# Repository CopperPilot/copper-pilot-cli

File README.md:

<div align="center">
  <a href="https://copperpilot.ai">
    <picture>
      <source media="(prefers-color-scheme: dark)" srcset="https://github.com/CopperPilot/copper-pilot-cli/blob/main/docs/assets/logo-dark.png?raw=true">
      <source media="(prefers-color-scheme: light)" srcset="https://github.com/CopperPilot/copper-pilot-cli/blob/main/docs/assets/logo-light.png?raw=true">
      
    </picture>
  </a>
</div>

<div align="center">
  <h3>The AI for PCB design, in your terminal.</h3>
</div>

<div align="center">

</div>

<div align="center">

</div>

<br>

CopperPilot in your terminal: a thin, open-source client for CopperPilot electronics design agent, the best AI for PCB Design.

## Prerequisites

- Python 3.11 or newer
- A [CopperPilot](https://copperpilot.ai) account for login
- KiCad 10 on `PATH` only if you run [`examples/001_esp32`](examples/001_esp32) or [`examples/002_cm5_camera`](examples/002_cm5_camera)

## Install and run

```console
pip install copper-pilot-cli
copper-pilot
```

To let the agent import LCSC/EasyEDA parts (symbol, footprint and 3D model) with
`easyeda2kicad`, install the optional extra, which is AGPL-3.0 licensed:
`pip install "copper-pilot-cli[easyeda]"` (or
`uv tool install "copper-pilot-cli[easyeda]"`). Agent shell commands can run
command-line tools installed alongside the CLI even when pipx or `uv tool` keeps
them off your `PATH`.

The first interactive launch opens a browser for CopperPilot device login.
With no path argument, the current directory is the workspace and a new chat
starts immediately. Any existing directory is valid.

CopperPilot checks for feature updates once per day without delaying your work.
When a release adds a feature, it prints one line with the feature and
`copper-pilot update`. Use `copper-pilot update --check` to inspect the latest
release, or `copper-pilot update` to run the owning package manager's update.

```console
copper-pilot ./my-board
copper-pilot --resume
copper-pilot threads list
copper-pilot -n -m "Review this board" --json
copper-pilot -n -r          # resume the most recent thread's unfinished turn
copper-pilot --mode plan --effort intelligence -m "Survey and plan this board"
```

Long turns survive dropped connections, server restarts and LLM provider rate
limits (the CLI shows "High demand — waiting to continue" and resumes on its
own): the CLI keeps a
journal of the turn on your machine and resumes it automatically. If a turn
still does not finish (or the CLI was closed mid-turn), type `/resume` in the
TUI, run `copper-pilot -n -r`, or send "continue"; the turn picks up where it
left off without re-running finished tools. See
[Turn durability](docs/cli.md#turn-durability).

Both `copper-pilot` and `copper-pilot-cli` run the same program.
`copper-pilot --help` lists flags; [docs/cli.md](docs/cli.md) is the full
command reference.

Balanced effort is the default. Paid-plan users can select Intelligence with
`--effort intelligence` or interactive `/effort`; Intelligence runs on Gemini 4
Argon. Picking another model (`--model <id>`, `/model`) is turned off for now
(`ENABLE_MODEL_SELECTOR` in `copper_models.py`). Intelligence uses
server-owned survey subagents and shows their lifecycle through the existing
Deep Agents task rows; Intelligence Plan turns survey before writing a plan.

## Validate

```console
copper-pilot validate ./my-board
```

Runs a stage-gated graph of read-only reviewers over the KiCad workspace:
`kicad-cli` checks (ERC, DRC, schematic parity, board rules, Gerbers) plus
hosted Agent-mode reviewers, each scoped to one concern, in the order a hardware
engineer reviews a board. It never edits design files. The verdict, a
`REPORT.md`, and `next_actions.json` (only the earliest failing stage, worst
first) land in `.copperpilot/validate/latest/`; `--emit-fix-prompt` prints a
ready message for `copper-pilot --mode agent`. Exit codes: 0 pass, 1 fail,
2 config error, 3 incomplete, 4 not logged in or usage limit. See
[docs/validate.md](docs/validate.md).

## Use from Claude Code, Cursor, or Codex

CopperPilot stays the electronics agent. Copy
[`skills/copper-pilot-review/SKILL.md`](skills/copper-pilot-review/SKILL.md) into
your harness, or expose the same agent over MCP:

```console
claude mcp add copper-pilot -- copper-pilot mcp
```

Claude Code can also install the in-repo plugin:

```text
/plugin marketplace add CopperPilot/copper-pilot-cli
/plugin install copper-pilot
```

That plugin starts `copper-pilot mcp` (tools `status`, `ask`, `plan`, `run`,
`resume`, `threads_list`, `validate`) and adds `@copper-pilot` plus
`/copper-pilot-review`. Editors that speak the Agent Client Protocol, such as
Zed, can run `copper-pilot acp` after `pip install "copper-pilot-cli[acp]"`.
Setup for Cursor, Codex, Zed, and approvals: [docs/harness.md](docs/harness.md).

## Configuration

- Production API: `https://copperpilot.ai`
- Development override: `COPPER_PILOT_API_URL`
- User state: `~/.copper-pilot/.state`
- Project artifacts: `.copperpilot/`

Credentials are stored in a private, atomically replaced `auth.json`; on POSIX
the parent directory is mode `0700` and the file is mode `0600`.

## LangChain

```python
from copper_pilot_cli.copper_protocol import CopperEffort, CopperMode
from copper_pilot_cli.langchain import CopperPilotAgent
from helper import drc_violations, erc_errors, render_pcb, run

PLAN = CopperMode.PLAN

copper_pilot = CopperPilotAgent(
    workspace="esp32",
    effort=CopperEffort.INTELLIGENCE,
    model="claude-opus-5-5",  # optional; Intelligence defaults to Gemini 4 Argon
)

run(copper_pilot, "Build me an ESP32 dev board.", PLAN)
run(copper_pilot, "Let us build this plan.")
run(copper_pilot, "Inspect the PCB, check for any missing 3D models, and apply them accordingly.")

assert erc_errors() == 0
assert drc_violations() == 0
render_pcb("esp32.png")
```

`CopperPilotAgent` is a `Runnable`, not a chat model. It represents a complete
hosted agent run, including local tool requests. Use `as_langgraph()` for graph
composition or `as_compiled_subagent()` for explicit delegation from an outer
Deep Agent. The compatible `deepagents` runtime is installed and pinned by this
package.

That snippet is the runnable example in
[`examples/001_esp32`](examples/001_esp32). A phased CM5 camera carrier lives in
[`examples/002_cm5_camera`](examples/002_cm5_camera).

## Security boundary

The hosted agent may request local filesystem and shell tools. Reads and
searches run freely. Writes, edits, deletes, and shell commands are gated by
Manual approval by default. Auto permits only deterministic routine actions;
unknown actions still ask. YOLO must be selected explicitly. Shell commands
that reach outside the workspace (`find /`, `grep -r ~`, other projects under
the home directory, `docker`, `sudo`, `ssh`, `pkill`) count as dangerous: they
ask unless you run YOLO or Auto with dangerous shell commands auto-allowed, and
otherwise are refused when nobody can approve them (headless, MCP). See
[docs/cli.md](docs/cli.md#outside-the-workspace).

Filesystem, search, edit, and shell execution use Deep Agents' native
`FilesystemMiddleware` tools and `LocalShellBackend`; CopperPilot's adapter only
normalizes hosted tool names, approval decisions, and result envelopes.

Computer use, model/provider selection, local model execution, LangSmith
tracing, content telemetry, MCP **host**/plugin-runtime controls, and server
implementation code are not part of this package. A thin MCP **server**
(`copper-pilot mcp`) and an ACP **server** (`copper-pilot acp`) that delegate
to the hosted agent are.

See [UPSTREAM.md](UPSTREAM.md) and [NOTICE](NOTICE) for the retained Textual
client attribution.

To report a vulnerability, see [SECURITY.md](SECURITY.md).

## Development

```console
pip install -e ".[dev]"
make fmt
make lint
make test
```

`make test` runs `pytest -m "not live"`. Live tests skip unless a CopperPilot
credential is stored. Release tagging is `make release`. Details:
[docs/development.md](docs/development.md).

## Contributing

Bug reports, features, and pull requests are welcome. Please read
[CONTRIBUTING.md](CONTRIBUTING.md) and the
[Code of Conduct](CODE_OF_CONDUCT.md). Use the
[bug report form](https://github.com/CopperPilot/copper-pilot-cli/issues/new?template=bug_report.yml)
so we can reproduce the problem.

## License

[MIT](LICENSE).

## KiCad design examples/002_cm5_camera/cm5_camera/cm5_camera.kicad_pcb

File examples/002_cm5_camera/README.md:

# CM5 Camera Carrier

English in. KiCad out. CM5 camera carrier. Clean ERC, clean DRC, rendered PCB.

```python
from copper_pilot_cli.copper_protocol import CopperMode
from copper_pilot_cli.langchain import CopperPilotAgent
from helper import (
    already_done,
    discard_stale_plan,
    drc_violations,
    erc_errors,
    ensure_outer_gnd_zones,
    footprints_have_3d_models,
    format_netlist_contract,
    format_placement_spec,
    hosted_plan_prompt,
    inject_feedback,
    libraries_ready,
    lock_diff_tracks,
    lock_placement,
    netlist_matches,
    pcb_matches_schematic,
    pcb_segment_count,
    placement_feedback,
    placement_matches_spec,
    plan_has_spec,
    refill_zones,
    render_pcb,
    repair_drc,
    repair_erc,
    reset_pcb_copper,
    restore_pcb_if_wiped,
    route_headless,
    run,
    snapshot_pcb,
    solidify_plane_pad_connections,
    start,
    strip_high_speed_from_planes,
    telemetry_prompt,
    unconnected_count,
    zones_and_rules_ready,
)

PLAN = CopperMode.PLAN

PLAN_PROMPT = hosted_plan_prompt()
LIBS_PROMPT = (
    "Set up symbols and footprints for this CM5 camera project, reverse-engineered "
    "from Waveshare CM4-NANO-C (https://www.waveshare.com/wiki/CM4-NANO-C) and "
    "aligned with https://github.com/rapidanalysis/xerxes DF40 practice. "
    "Goal: project libraries must include every BOM row from the plan."
)
SCHEMATIC_PROMPT = (
    "Implement schematic capture in cm5_camera/cm5_camera.kicad_sch. "
    "Goal: kicad-cli `sch export netlist --format kicadxml` must contain these "
    "nets and connections:\\n"
    f"{format_netlist_contract()}\\n"
    "Use those net names. Populate Type_C1, U5, U1-U3, X1, Q1/Q2, L1-L3, J1 IMX219, "
    "U6, HDMI1, DSI1, TF1, PI1, Key1, and the CM5 DF40 module."
)
ERC_PROMPT = (
    "Run kicad-cli sch erc on cm5_camera/cm5_camera.kicad_sch and fix pin types, "
    "power flags, and floating inputs. Goal: zero ERC errors."
)
UPDATE_PCB_PROMPT = (
    "Update PCB footprints from the schematic. Goal: every schematic symbol with a "
    "footprint is on cm5_camera/cm5_camera.kicad_pcb, extra footprints are removed, "
    "and the netlist is imported."
)
LAYOUT_PROMPT = (
    "Lay out cm5_camera/cm5_camera.kicad_pcb from a wiped copper state. "
    "Goal: Edge.Cuts 55.0 x 40.0 mm with 3.0 mm corner radii and 4x M2.5 holes at "
    "board-local 3.5,3.5 / 3.5,36.5 / 51.5,3.5 / 51.5,36.5. Place and lock "
    "footprints to this board-local table (origin = SW of Edge.Cuts). J1 is east "
    "of center, not the board middle. HDMI1/DSI1 north, J2 east, TF1 west, "
    "Type_C1 south-west, PI1 west, Key1 south-east, DF40 on B.Cu. Silk: CM5 CAMERA.\\n"
    f"{format_placement_spec()}"
)
ZONES_PROMPT = (
    "Configure the 6-layer SIG-GND-SIG-PWR-GND-SIG stackup and pour planes. "
    "Goal: F.Cu, In1.Cu, In2.Cu, In3.Cu, In4.Cu, B.Cu present; solid GND zone on "
    "In1.Cu and In4.Cu; split CM5_5V and PWR_3V3 zones on In3.Cu; netclasses "
    "100Ohm_Diff (0.15 mm / 0.18 mm gap), 90Ohm_Diff (0.18 mm / 0.20 mm), "
    "Power_5V, Power_3V3 in cm5_camera.kicad_pro; refill zones. Do not autoroute."
)
ACK_PROMPT = (
    "Reply with the single word OK. Do not call tools. Do not edit files. "
    "Do not run kicad_autorouter or FreeRouting. Local headless routing already "
    "imported copper."
)
MODELS_3D_PROMPT = (
    "Inspect kicad-cli pcb render of cm5_camera/cm5_camera.kicad_pcb and assign "
    "3D models. Goal: the CM5 module, IMX219, Mini-HDMI, USB-C, USB-A, Micro SD, "
    "and GPIO header all have 3D models; re-render the top side."
)

copper_pilot = CopperPilotAgent(workspace="cm5_camera")
start(copper_pilot)
discard_stale_plan()
if not already_done(plan_has_spec):
    run(copper_pilot, PLAN_PROMPT, PLAN)
assert plan_has_spec()
if not already_done(libraries_ready):
    run(copper_pilot, LIBS_PROMPT)
assert libraries_ready()
if not already_done(netlist_matches):
    run(copper_pilot, SCHEMATIC_PROMPT)
assert netlist_matches()
if not already_done(lambda: erc_errors() == 0):
    run(copper_pilot, ERC_PROMPT)
    repair_erc()
assert erc_errors() == 0
if not already_done(pcb_matches_schematic):
    run(copper_pilot, UPDATE_PCB_PROMPT)
assert pcb_matches_schematic()

has_routes = pcb_segment_count() >= 50
keep_zones = already_done(placement_matches_spec) and already_done(zones_and_rules_ready)
if not has_routes:
    reset_pcb_copper(keep_zones=keep_zones)
    inject_feedback(
        "Tracks and vias were wiped"
        + ("." if keep_zones else ", along with zones.")
        + " Rebuild layout, stackup, and routing from the CM5 camera spec in this "
        "same conversation."
    )
if not already_done(placement_matches_spec):
    run(copper_pilot, LAYOUT_PROMPT)
    if not already_done(placement_matches_spec):
        run(copper_pilot, placement_feedback())
    if not already_done(placement_matches_spec):
        locked = lock_placement()
        inject_feedback(
            "Locked these footprints to the board-local assembly table: "
            + ", ".join(locked)
            + ". Continue from this placement; do not scatter parts."
        )
assert placement_matches_spec()

if not already_done(zones_and_rules_ready):
    run(copper_pilot, ZONES_PROMPT)
    if not already_done(zones_and_rules_ready):
        run(
            copper_pilot,
            "Finish the 6-layer stackup, 100Ohm_Diff / 90Ohm_Diff / Power_5V / "
            "Power_3V3 netclasses, GND pours on In1.Cu and In4.Cu, and CM5_5V plus "
            "PWR_3V3 pours on In3.Cu. Do not autoroute.",
        )
assert zones_and_rules_ready()

if not has_routes:
    diffs = route_headless(stage="diffs")
    if strip_high_speed_from_planes():
        diffs = route_headless(stage="diffs", passes=3)
        strip_high_speed_from_planes()
    lock_diff_tracks()
    leftover = unconnected_count()
    copper = snapshot_pcb()
    inject_feedback(telemetry_prompt(diffs, leftover=leftover))
    run(copper_pilot, ACK_PROMPT)
    restore_pcb_if_wiped(copper)
    assert high_speed_not_on_planes()

ensure_outer_gnd_zones()
solidify_plane_pad_connections()
if pcb_segment_count() < 700:
    gpio = route_headless(stage="gpio")
    if unconnected_count() > 0:
        gpio = route_headless(stage="gpio", passes=12)
    leftover = unconnected_count()
    copper = snapshot_pcb()
    inject_feedback(telemetry_prompt(gpio, leftover=leftover))
    run(copper_pilot, ACK_PROMPT)
    restore_pcb_if_wiped(copper)
refill_zones()
if drc_violations():
    repair_drc()
if not already_done(footprints_have_3d_models):
    run(copper_pilot, MODELS_3D_PROMPT)
assert footprints_have_3d_models()
render_pcb("cm5_camera.png")
assert high_speed_not_on_planes()
assert drc_violations() == 0
leftover = unconnected_count()
assert leftover == 0, f"{leftover} unconnected items remain"
```

```console
python examples/002_cm5_camera/main.py
```

Python 3.11+, `pip install -e .`, `copper-pilot auth login`, and KiCad 10 on `PATH`.

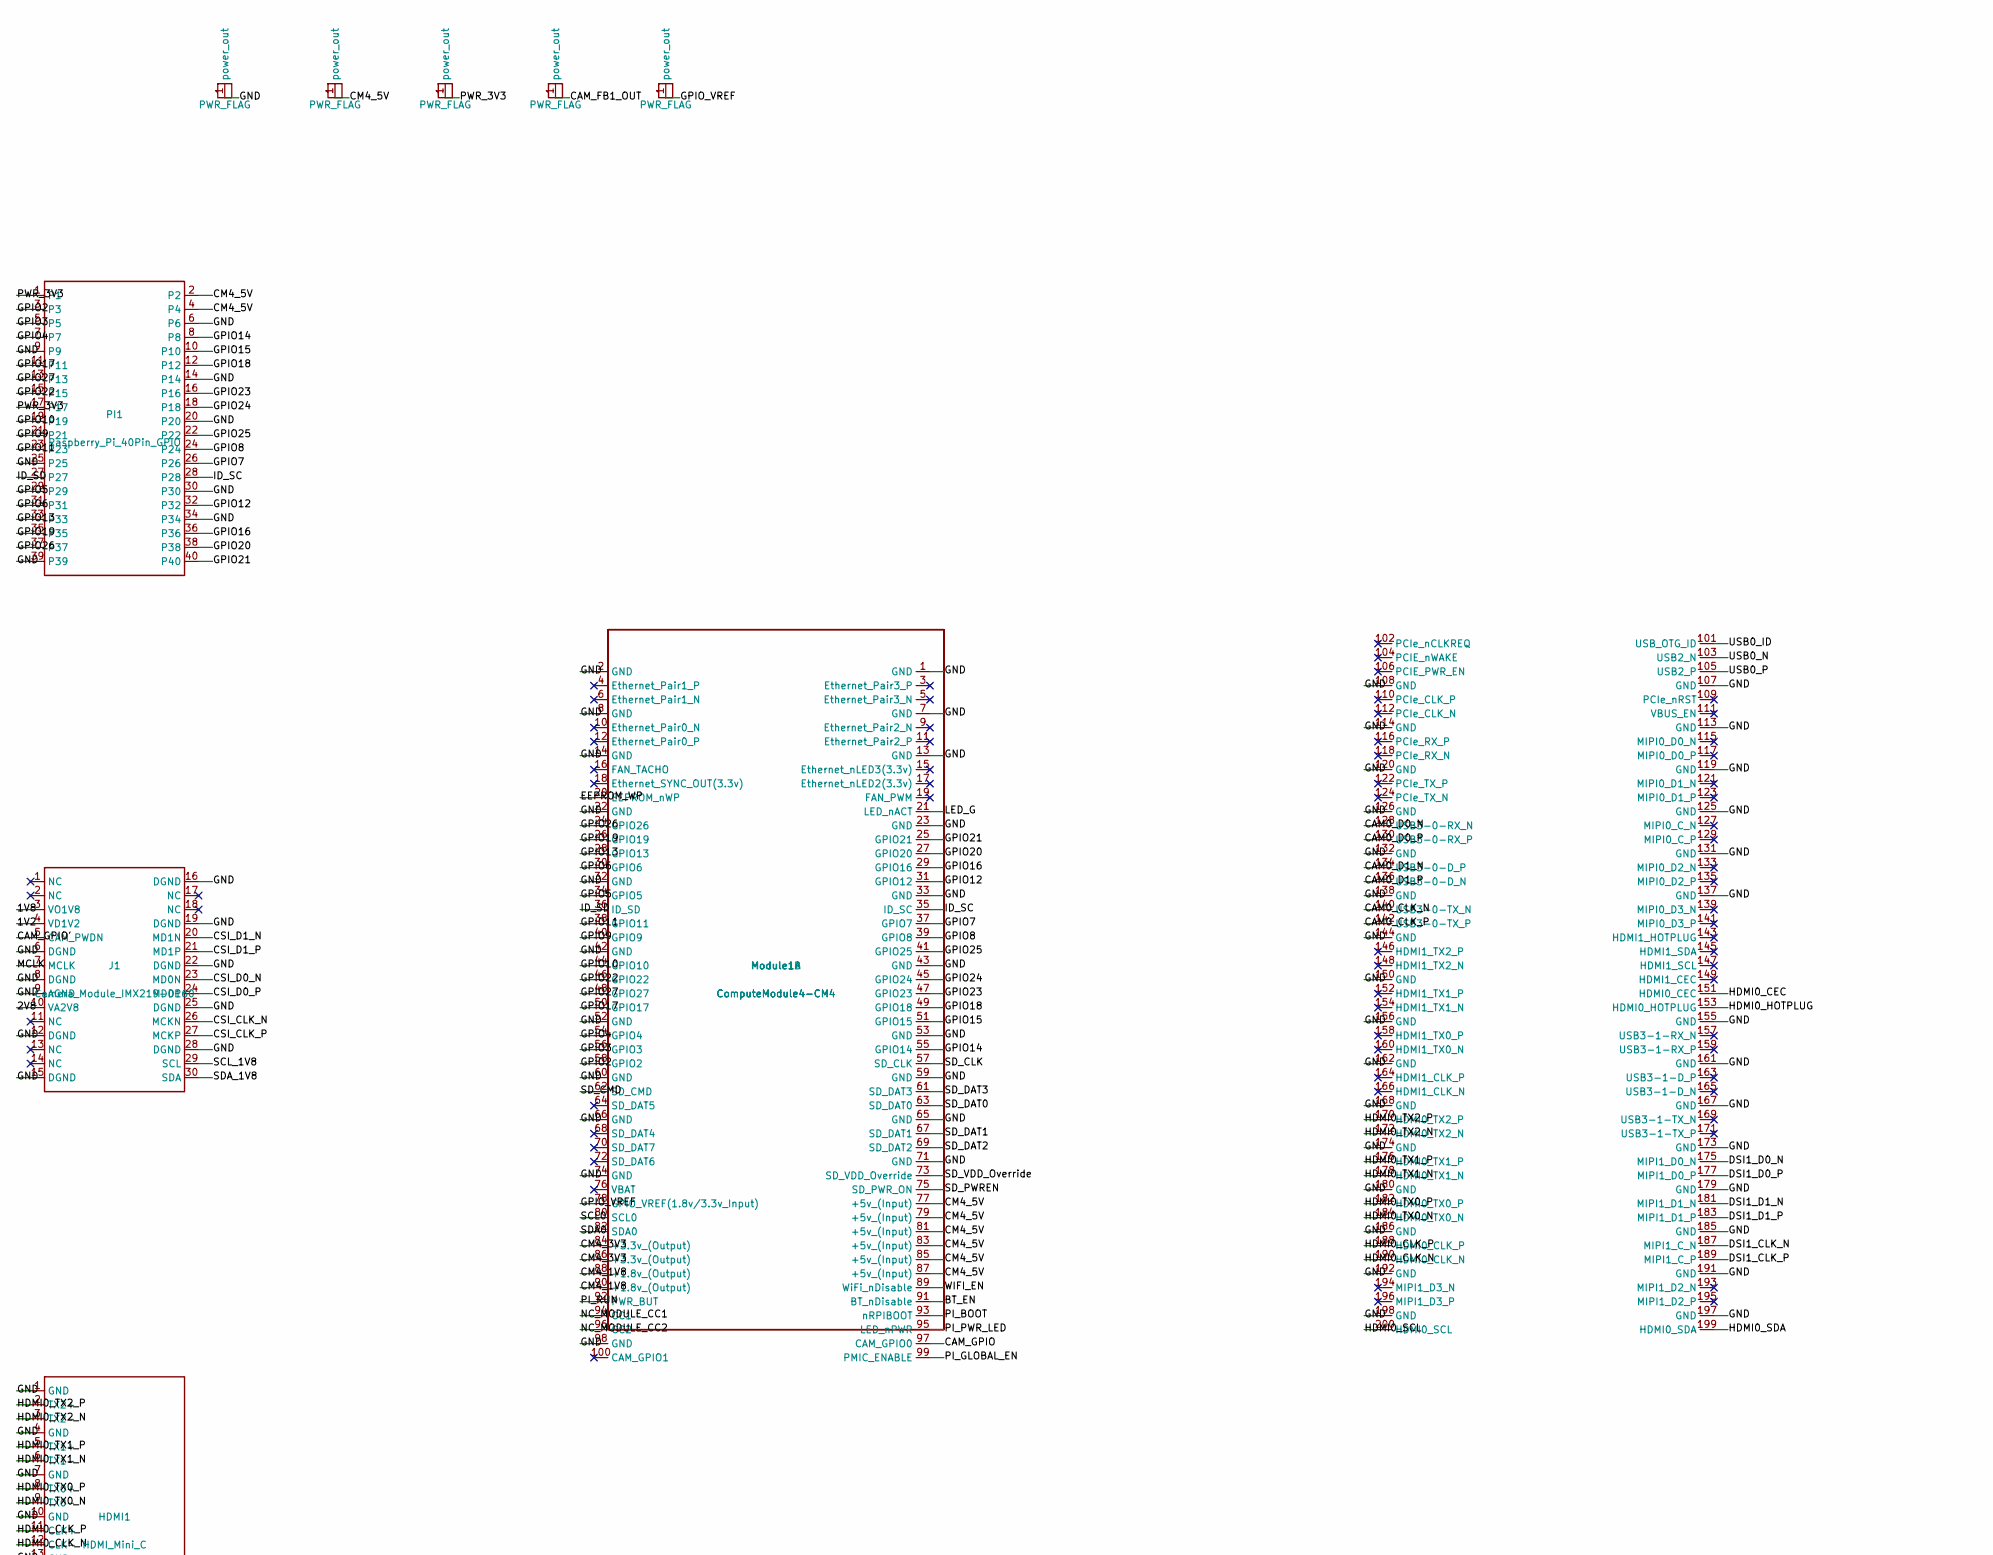
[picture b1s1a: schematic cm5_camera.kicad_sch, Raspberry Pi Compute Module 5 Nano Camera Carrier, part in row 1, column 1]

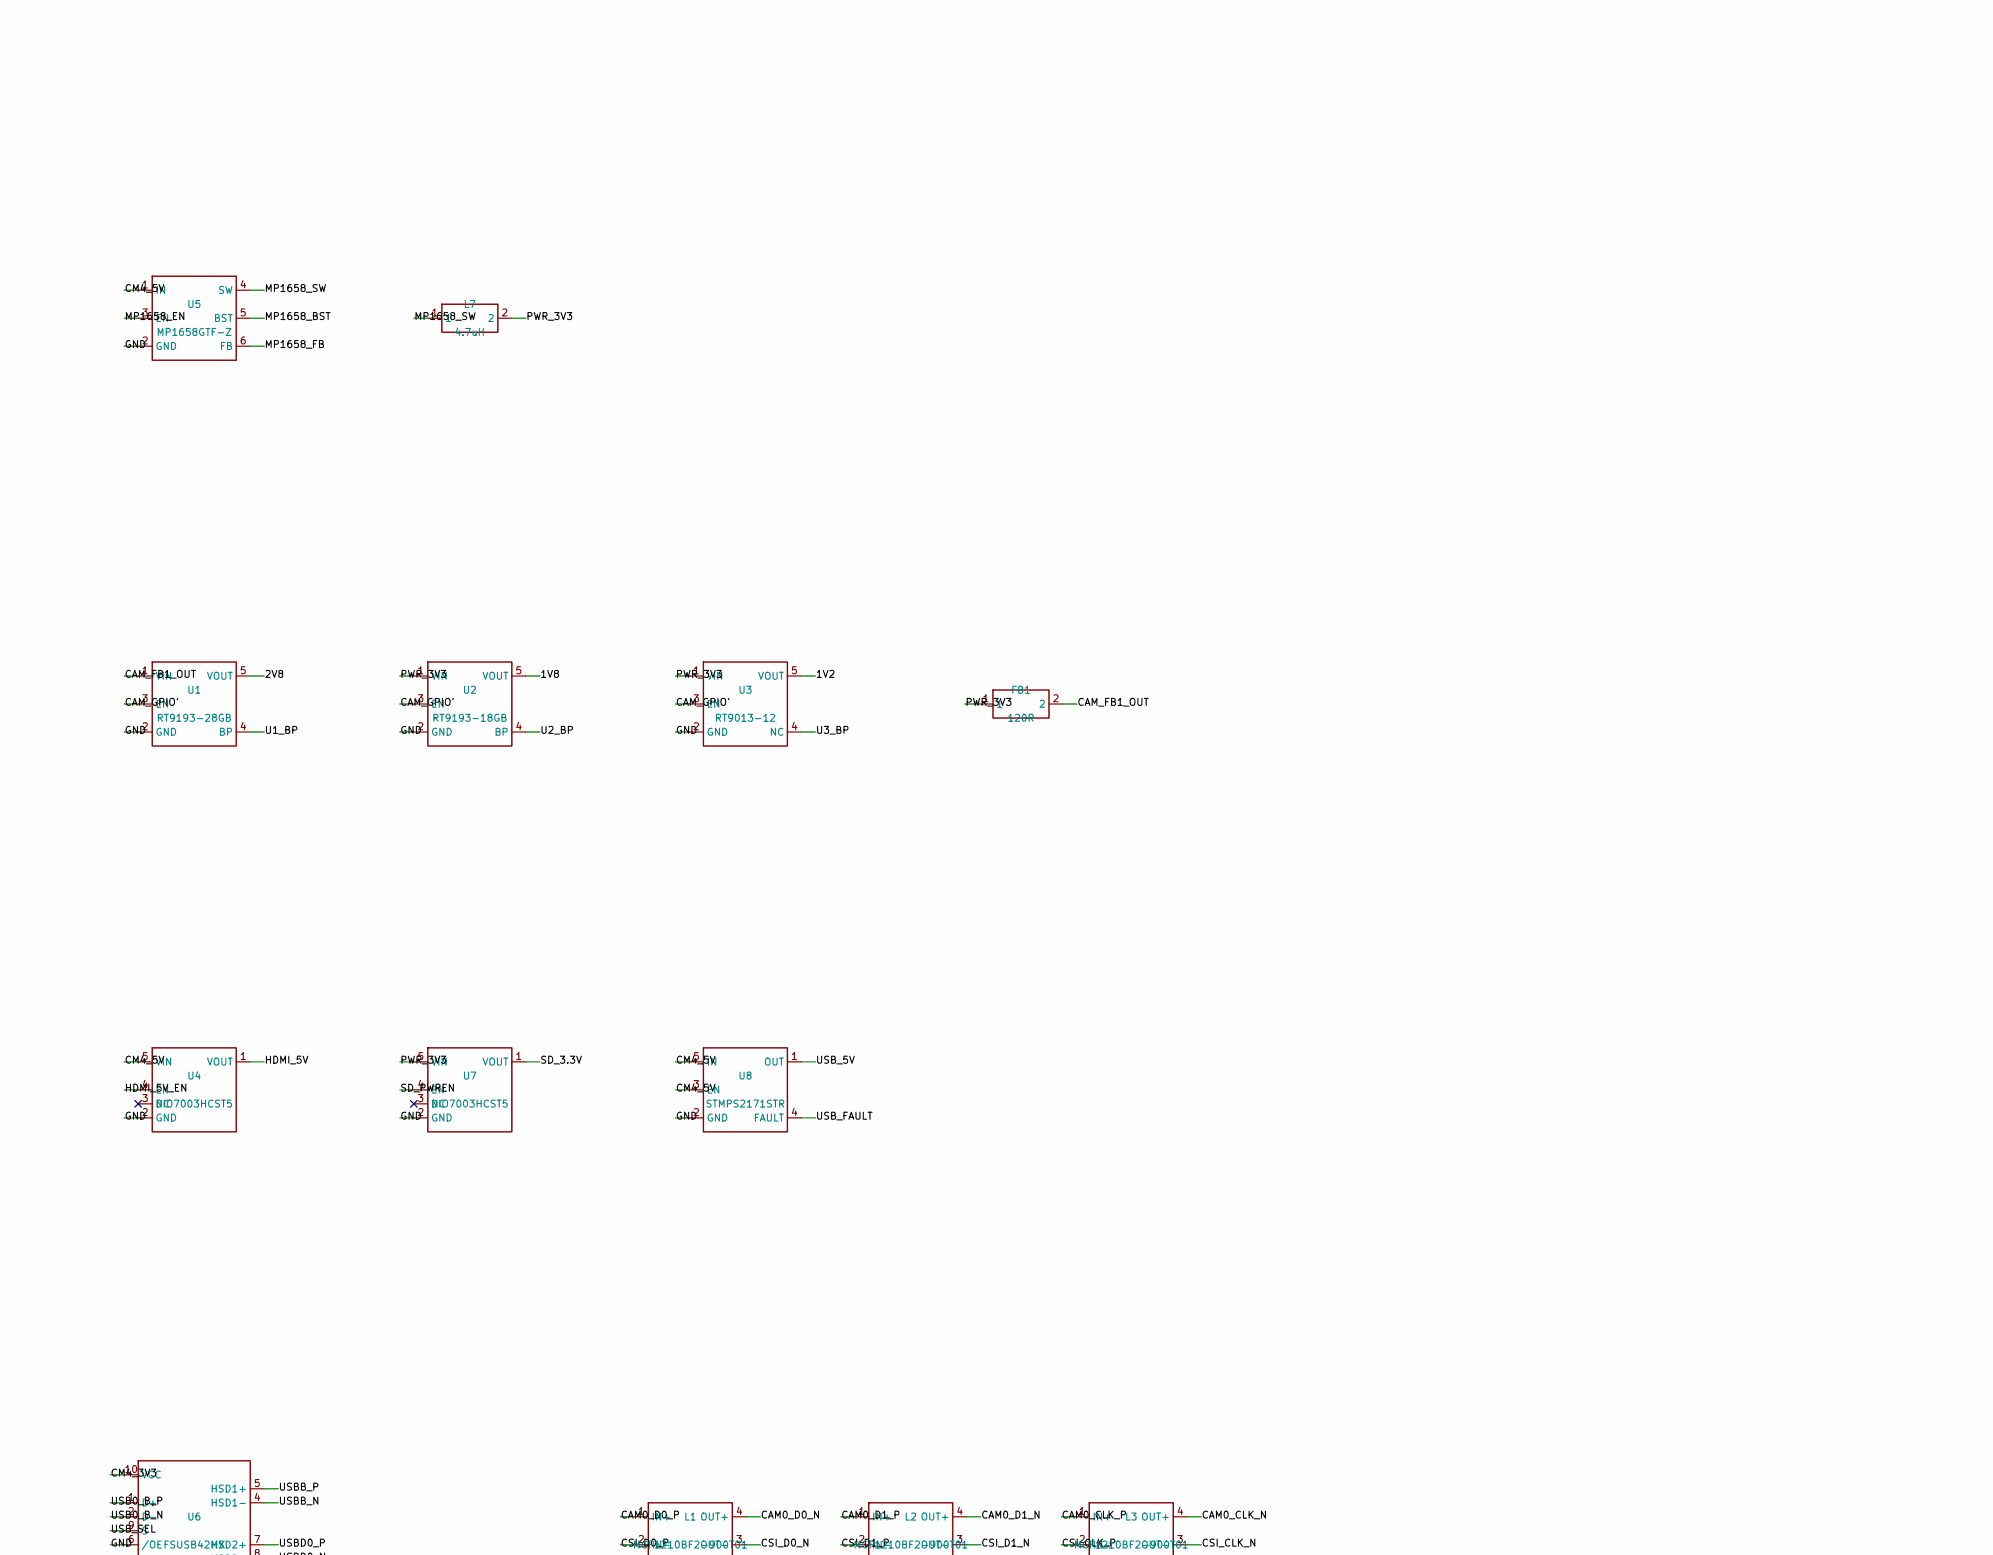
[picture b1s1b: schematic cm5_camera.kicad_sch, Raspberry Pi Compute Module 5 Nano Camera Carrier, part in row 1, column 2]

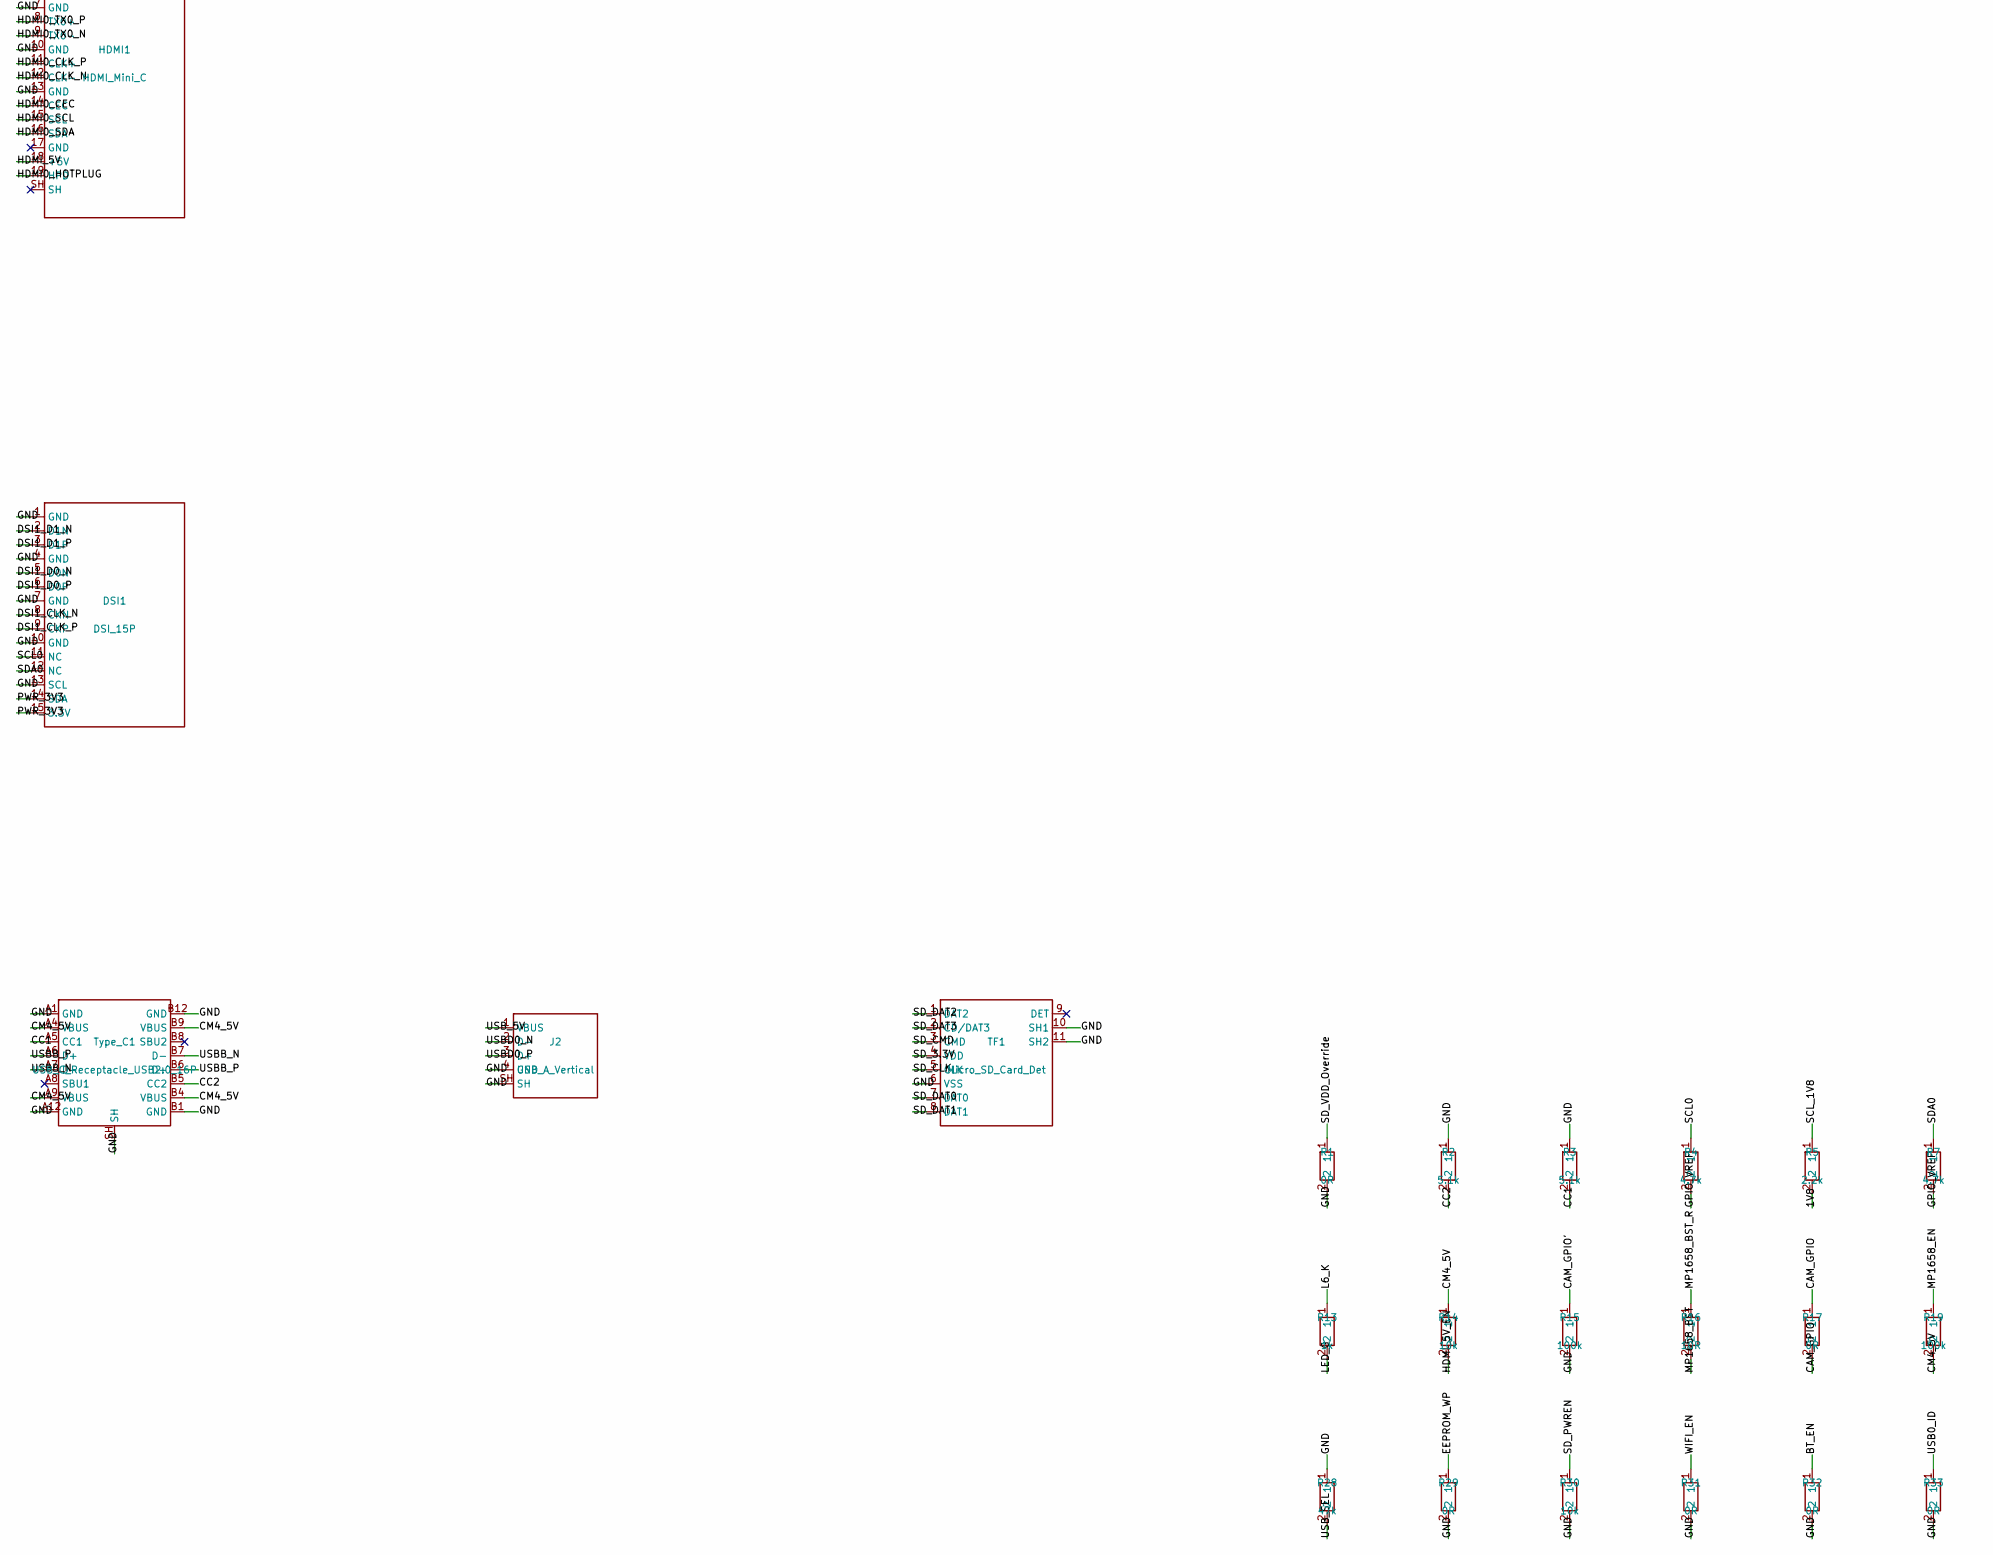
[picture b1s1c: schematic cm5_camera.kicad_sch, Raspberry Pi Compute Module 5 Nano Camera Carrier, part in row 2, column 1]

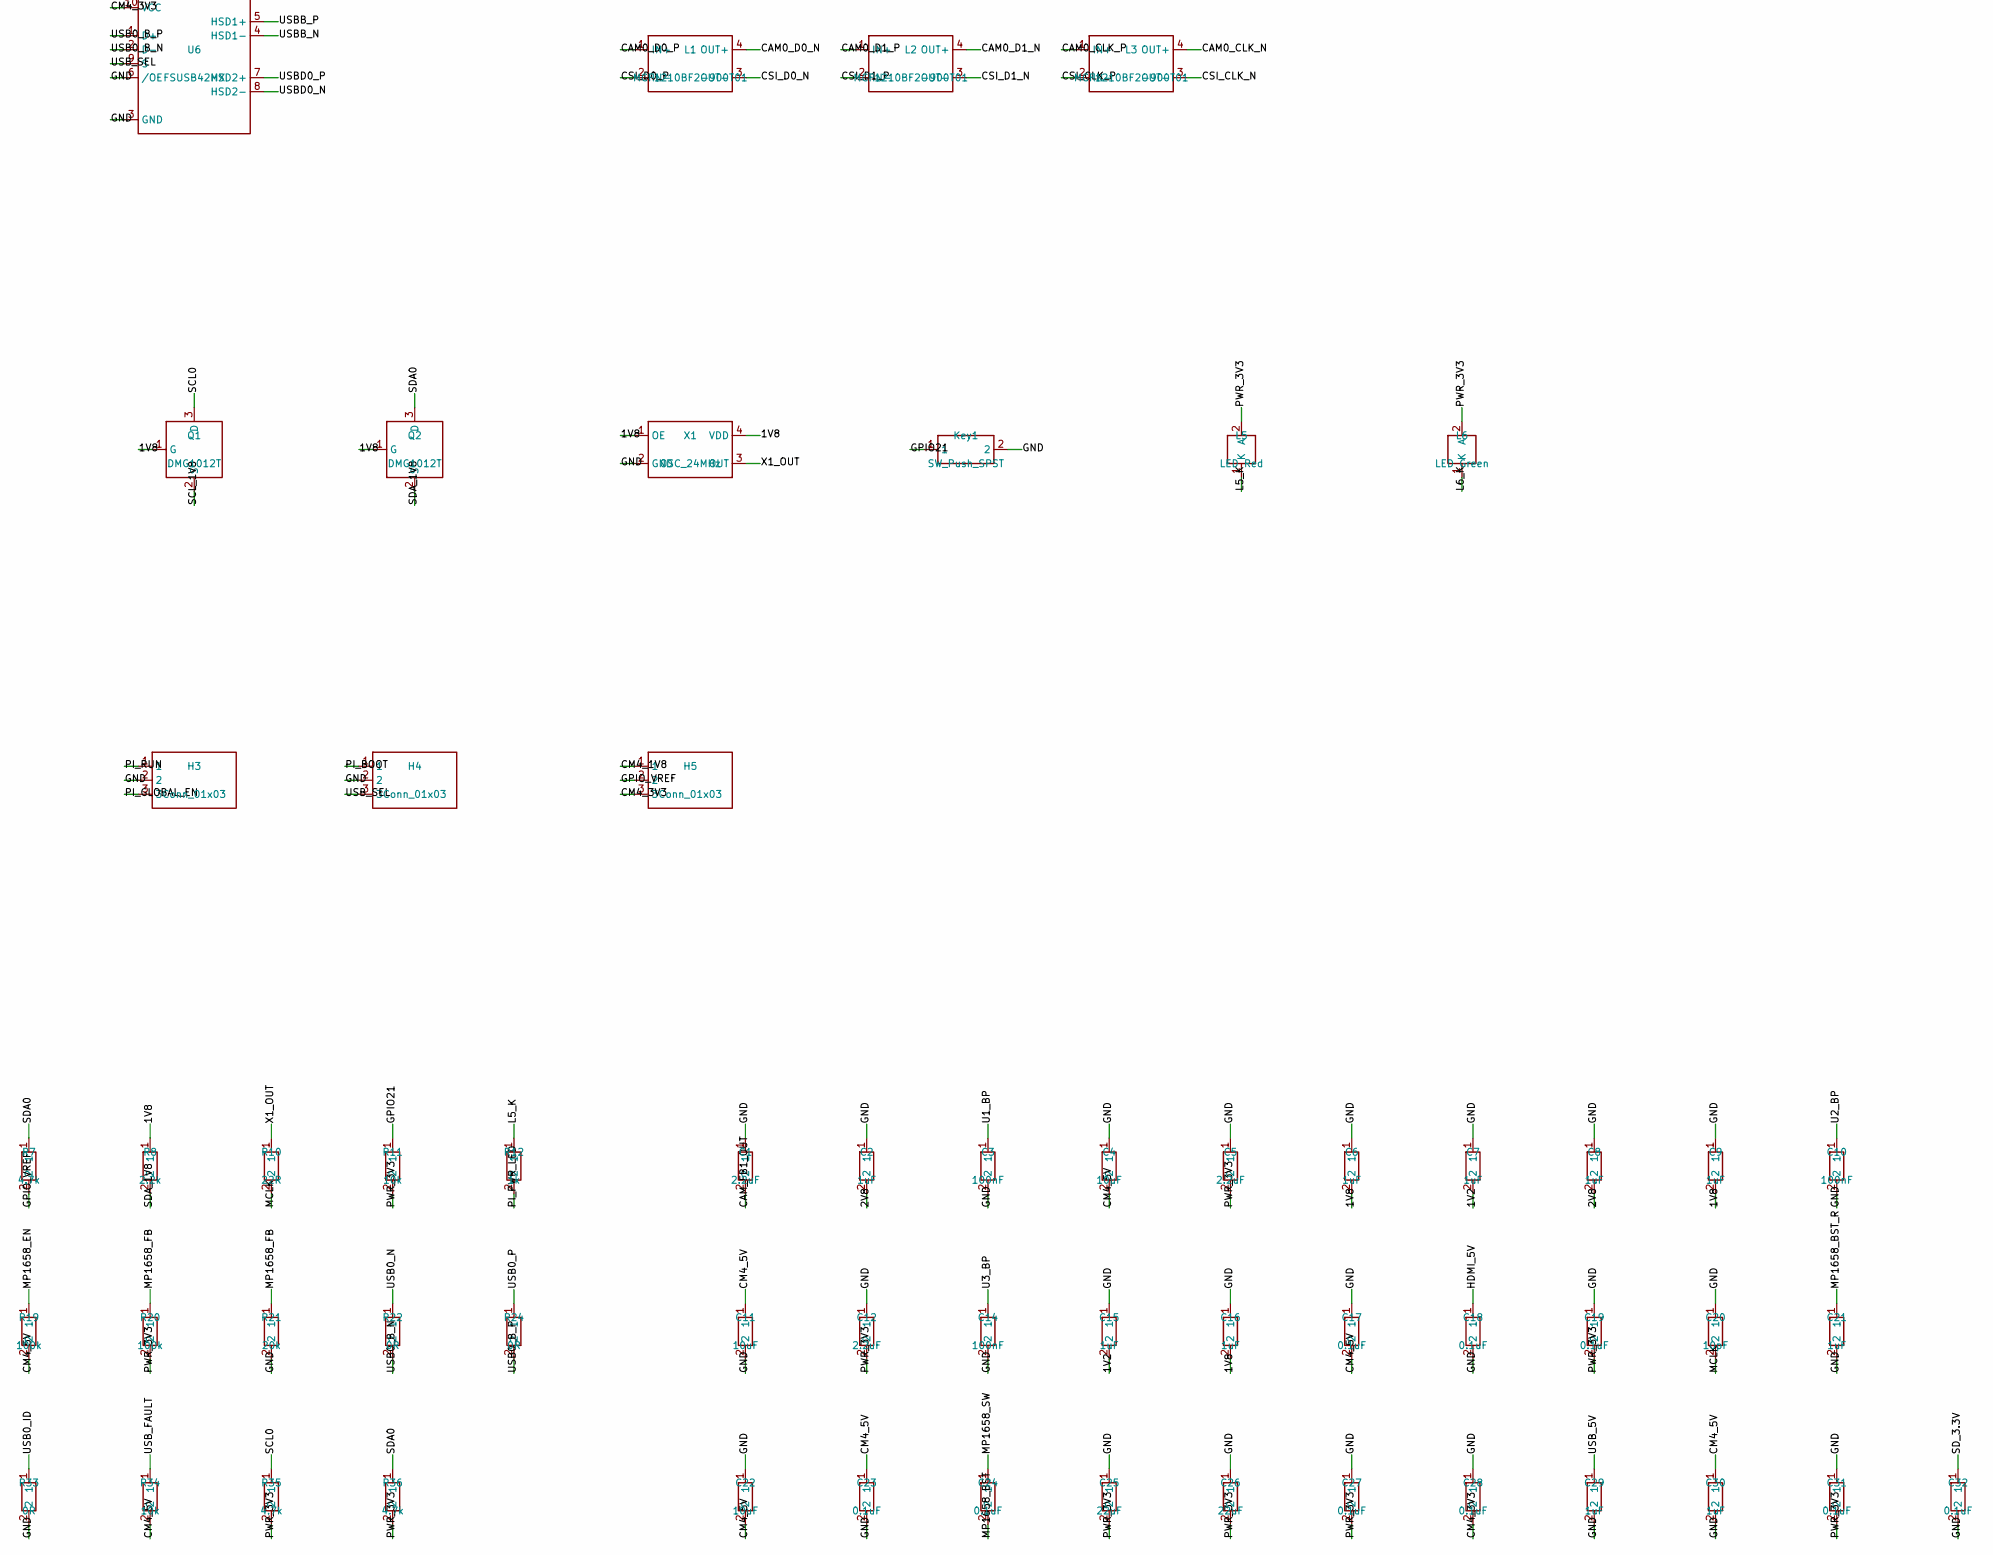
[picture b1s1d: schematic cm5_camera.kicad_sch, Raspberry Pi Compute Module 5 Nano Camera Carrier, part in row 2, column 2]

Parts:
C1, C5, C12: 2.2uF; C_0402_1005Metric
C2, C6, C7, C8, C9, C15, C16, C21, C29, C30: 1uF; C_0402_1005Metric
C3, C10, C14: 100nF; C_0402_1005Metric
C4, C11, C22: 10uF; C_0805_2012Metric
C17, C18, C19, C23, C24, C27, C28, C31, C32: 0.1uF; C_0402_1005Metric
C20: 10pF; C_0402_1005Metric
C25, C26: 22uF; C_0805_2012Metric
DSI1: DSI_15P; Molex_200528-0150_1x15-1MP_P1.00mm_Horizontal
FB1: 120R; R_0603_1608Metric
H3, H4, H5: Conn_01x03; PinHeader_1x03_P2.54mm_Vertical
HDMI1: HDMI_Mini_C; HDMI_Mini-C_Molex_47151-0001
J1: Camera_Module_IMX219-D160
J2: USB_A_Vertical; MOLEX_USB_67298-4090
Key1: SW_Push_SPST; SW_SPST_PTS645Sx43SMTR92
L1, L2, L3: MCF1210BF2-900T01; L_CommonModeChoke_Coilank_ACM1210
L5: LED Red; LED_0603_1608Metric
L6: LED Green; LED_0603_1608Metric
L7: 4.7uH; L_Bourns_SRP5030CC
Module1: ComputeModule4-CM4; Raspberry-Pi-4-Compute-Module
PI1: Raspberry_Pi_40Pin_GPIO; PinHeader_2x20_P2.54mm_Vertical
Q1, Q2: DMG1012T; Texas_DRT-3
R1, R17, R22, R24, R29, R31, R32, R33: 0R; R_0402_1005Metric
R2, R3: 5.1k; R_0402_1005Metric
R4, R7, R35, R36: 4.7k; R_0402_1005Metric
R5, R8: 2.2k; R_0402_1005Metric
R10: 22R; R_0402_1005Metric
R11, R14, R30, R34: 10k; R_0402_1005Metric
R12, R13: 1k; R_0402_1005Metric
R15, R19, R20: 100k; R_0402_1005Metric
R16: 10R; R_0402_1005Metric
R21: 20k; R_0402_1005Metric
R28: 47k; R_0402_1005Metric
TF1: Micro_SD_Card_Det; SDCARD_MOLEX_503398-1892
Type_C1: USB_C_Receptacle_USB2.0_16P; USB_C_Receptacle_GCT_USB4105-xx-A_16P_TopMnt_Horizontal
U1: RT9193-28GB; SOT-23-5
U2: RT9193-18GB; SOT-23-5
U3: RT9013-12; SOT-23-5
U4, U7: DIO7003HCST5; SOT-23-5
U5: MP1658GTF-Z; TSOT-23-6
U6: FSUSB42MX; UQFN-10_1.4x1.8mm_P0.4mm
U8: STMPS2171STR; SOT-23-5
X1: OSC_24MHz; Crystal_SMD_3225-4Pin_3.2x2.5mm

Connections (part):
/1V2: C7.2, C15.2, J1.4 (VD1V2), U3.5 (VOUT)
/1V8: C6.2, C9.2, C16.2, J1.3 (VO1V8), Q1.1 (G), Q2.1 (G), R5.2, R8.1, U2.5 (VOUT), X1.1 (OE), X1.4 (VDD)
/2V8: C2.2, C8.2, J1.10 (VA2V8), U1.5 (VOUT)
/BT_EN: Module1.91 (BT_nDisable), R32.1
/CAM0_CLK_N: L3.4 (OUT+), Module1.140 (USB3-0-TX_N)
/CAM0_CLK_P: L3.1 (IN+), Module1.142 (USB3-0-TX_P)
/CAM0_D0_N: L1.4 (OUT+), Module1.128 (USB3-0-RX_N)
/CAM0_D0_P: L1.1 (IN+), Module1.130 (USB3-0-RX_P)
/CAM0_D1_N: L2.4 (OUT+), Module1.134 (USB3-0-D_P)
/CAM0_D1_P: L2.1 (IN+), Module1.136 (USB3-0-D_N)
/CAM_FB1_OUT: C1.2, FB1.2, U1.1 (VIN)
/CAM_GPIO: Module1.97 (CAM_GPIO0), R17.1
/CAM_GPIO': J1.5 (CAM_PWDN), R15.1, R17.2, U1.3 (EN), U2.3 (EN), U3.3 (EN)
/CC1: R3.2, Type_C1.A5 (CC1)
/CC2: R2.2, Type_C1.B5 (CC2)
/CM4_1V8: H5.1, Module1.88 (+1.8v_(Output)), Module1.90 (+1.8v_(Output))
/CM4_3V3: C28.2, H5.3, Module1.84 (+3.3v_(Output)), Module1.86 (+3.3v_(Output)), U6.10 (VCC)
/CM4_5V: C4.2, C11.1, C17.2, C22.2, C23.1, C30.1, Module1.77 (+5v_(Input)), Module1.79 (+5v_(Input)), Module1.81 (+5v_(Input)), Module1.83 (+5v_(Input)), Module1.85 (+5v_(Input)), Module1.87 (+5v_(Input)), PI1.2, PI1.4, R14.1, R19.2, R34.2, Type_C1.A4 (VBUS), Type_C1.A9 (VBUS), Type_C1.B4 (VBUS), Type_C1.B9 (VBUS), U4.5 (VIN), U5.1 (IN), U8.3 (EN), U8.5 (IN)
/CSI_CLK_N: J1.26 (MCKN), L3.3 (OUT-)
/CSI_CLK_P: J1.27 (MCKP), L3.2 (IN-)
/CSI_D0_N: J1.23 (MD0N), L1.3 (OUT-)
/CSI_D0_P: J1.24 (MD0P), L1.2 (IN-)
/CSI_D1_N: J1.20 (MD1N), L2.3 (OUT-)
/CSI_D1_P: J1.21 (MD1P), L2.2 (IN-)
/DSI1_CLK_N: DSI1.8 (CKN), Module1.187 (MIPI1_C_N)
/DSI1_CLK_P: DSI1.9 (CKP), Module1.189 (MIPI1_C_P)
/DSI1_D0_N: DSI1.5 (D0N), Module1.175 (MIPI1_D0_N)
/DSI1_D0_P: DSI1.6 (D0P), Module1.177 (MIPI1_D0_P)
/DSI1_D1_N: DSI1.2 (D1N), Module1.181 (MIPI1_D1_N)
/DSI1_D1_P: DSI1.3 (D1P), Module1.183 (MIPI1_D1_P)
/EEPROM_WP: Module1.20 (EEPROM_nWP), R29.1
/GPIO2: Module1.58 (GPIO2), PI1.3
/GPIO3: Module1.56 (GPIO3), PI1.5
/GPIO4: Module1.54 (GPIO4), PI1.7
/GPIO5: Module1.34 (GPIO5), PI1.29
/GPIO6: Module1.30 (GPIO6), PI1.31
/GPIO7: Module1.37 (GPIO7), PI1.26
/GPIO8: Module1.39 (GPIO8), PI1.24
/GPIO9: Module1.40 (GPIO9), PI1.21
/GPIO10: Module1.44 (GPIO10), PI1.19
/GPIO11: Module1.38 (GPIO11), PI1.23
/GPIO12: Module1.31 (GPIO12), PI1.32
/GPIO13: Module1.28 (GPIO13), PI1.33
/GPIO14: Module1.55 (GPIO14), PI1.8
/GPIO15: Module1.51 (GPIO15), PI1.10
/GPIO16: Module1.29 (GPIO16), PI1.36
/GPIO17: Module1.50 (GPIO17), PI1.11
/GPIO18: Module1.49 (GPIO18), PI1.12
/GPIO19: Module1.26 (GPIO19), PI1.35
/GPIO20: Module1.27 (GPIO20), PI1.38
/GPIO21: Key1.1, Module1.25 (GPIO21), PI1.40, R11.1
/GPIO22: Module1.46 (GPIO22), PI1.15
/GPIO23: Module1.47 (GPIO23), PI1.16
/GPIO24: Module1.45 (GPIO24), PI1.18
/GPIO25: Module1.41 (GPIO25), PI1.22
/GPIO26: Module1.24 (GPIO26), PI1.37
/GPIO27: Module1.48 (GPIO27), PI1.13
/GPIO_VREF: H5.2, Module1.78 (GPIO_VREF(1.8v/3.3v_Input)), R4.2, R7.2
/HDMI0_CEC: HDMI1.14 (CEC), Module1.151 (HDMI0_CEC)
/HDMI0_CLK_N: HDMI1.12 (CLK-), Module1.190 (HDMI0_CLK_N)
/HDMI0_CLK_P: HDMI1.11 (CLK+), Module1.188 (HDMI0_CLK_P)
/HDMI0_HOTPLUG: HDMI1.19 (HPD), Module1.153 (HDMI0_HOTPLUG)
/HDMI0_SCL: HDMI1.15 (SCL), Module1.200 (HDMI0_SCL)
/HDMI0_SDA: HDMI1.16 (SDA), Module1.199 (HDMI0_SDA)
/HDMI0_TX0_N: HDMI1.9 (TX0-), Module1.184 (HDMI0_TX0_N)
/HDMI0_TX0_P: HDMI1.8 (TX0+), Module1.182 (HDMI0_TX0_P)
/HDMI0_TX1_N: HDMI1.6 (TX1-), Module1.178 (HDMI0_TX1_N)
/HDMI0_TX1_P: HDMI1.5 (TX1+), Module1.176 (HDMI0_TX1_P)
/HDMI0_TX2_N: HDMI1.3 (TX2-), Module1.172 (HDMI0_TX2_N)
/HDMI0_TX2_P: HDMI1.2 (TX2+), Module1.170 (HDMI0_TX2_P)
/HDMI_5V: C18.1, HDMI1.18 (+5V), U4.1 (VOUT)
/HDMI_5V_EN: R14.2, U4.4 (EN)
/ID_SC: Module1.35 (ID_SC), PI1.28
/ID_SD: Module1.36 (ID_SD), PI1.27
/L5_K: L5.1 (K), R12.1
/L6_K: L6.1 (K), R13.1
/LED_G: Module1.21 (LED_nACT), R13.2
/MCLK: C20.2, J1.7 (MCLK), R10.2
/MP1658_BST: C24.2, R16.2, U5.5 (BST)
/MP1658_BST_R: C21.1, R16.1
/MP1658_EN: R19.1, U5.3 (EN)
/MP1658_FB: R20.1, R21.1, U5.6 (FB)
/MP1658_SW: C24.1, L7.1, U5.4 (SW)
/PI_BOOT: H4.1, Module1.93 (nRPIBOOT)
/PI_GLOBAL_EN: H3.3, Module1.99 (PMIC_ENABLE)
/PI_PWR_LED: Module1.95 (LED_nPWR), R12.2
/PI_RUN: H3.1, Module1.92 (PWR_BUT)
/PWR_3V3: C5.2, C12.2, C19.2, C25.2, C26.2, C27.2, C31.2, DSI1.14 (SDA), DSI1.15 (3.3V), FB1.1, L5.2 (A), L6.2 (A), L7.2, PI1.1, PI1.17, R11.2, R20.2, R35.2, R36.2, U2.1 (VIN), U3.1 (VIN), U7.5 (VIN)
/SCL0: DSI1.11 (NC), Module1.80 (SCL0), Q1.3 (D), R4.1, R35.1
/SCL_1V8: J1.29 (SCL), Q1.2 (S), R5.1
/SDA0: DSI1.12 (NC), Module1.82 (SDA0), Q2.3 (D), R7.1, R36.1
/SDA_1V8: J1.30 (SDA), J1.SH, Q2.2 (S), R8.2
/SD_3.3V: C32.1, TF1.4 (VDD), U7.1 (VOUT)
/SD_CLK: Module1.57 (SD_CLK), TF1.5 (CLK)
/SD_CMD: Module1.62 (SD_CMD), TF1.3 (CMD)
/SD_DAT0: Module1.63 (SD_DAT0), TF1.7 (DAT0)
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

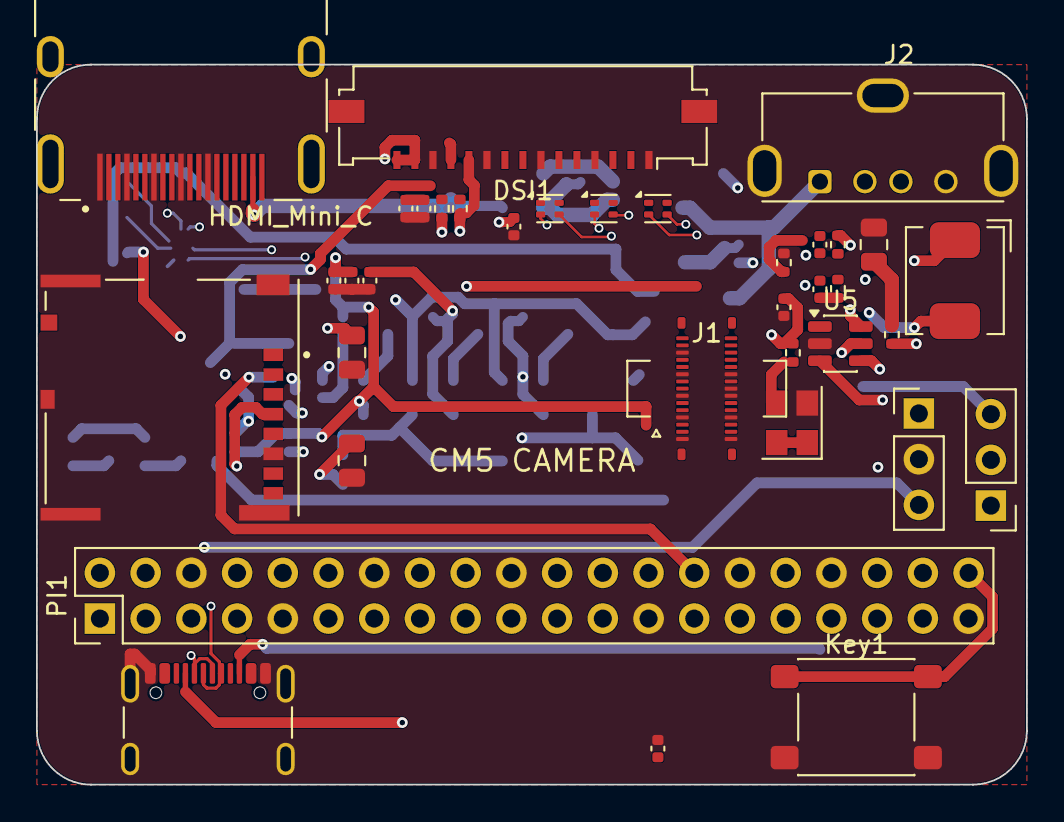
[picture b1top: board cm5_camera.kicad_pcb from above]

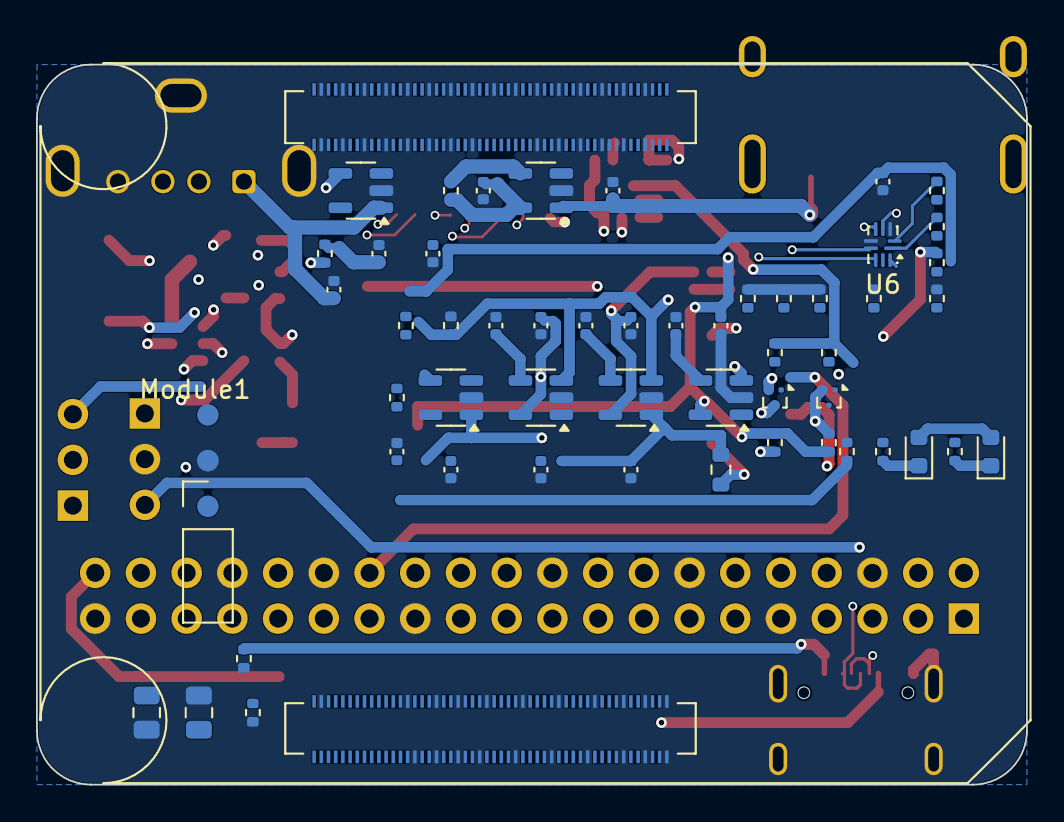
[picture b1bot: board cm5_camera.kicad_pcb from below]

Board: 6 copper layers, 55.0 x 40.0 mm, 90 parts (54 on the bottom side), 120 nets.
